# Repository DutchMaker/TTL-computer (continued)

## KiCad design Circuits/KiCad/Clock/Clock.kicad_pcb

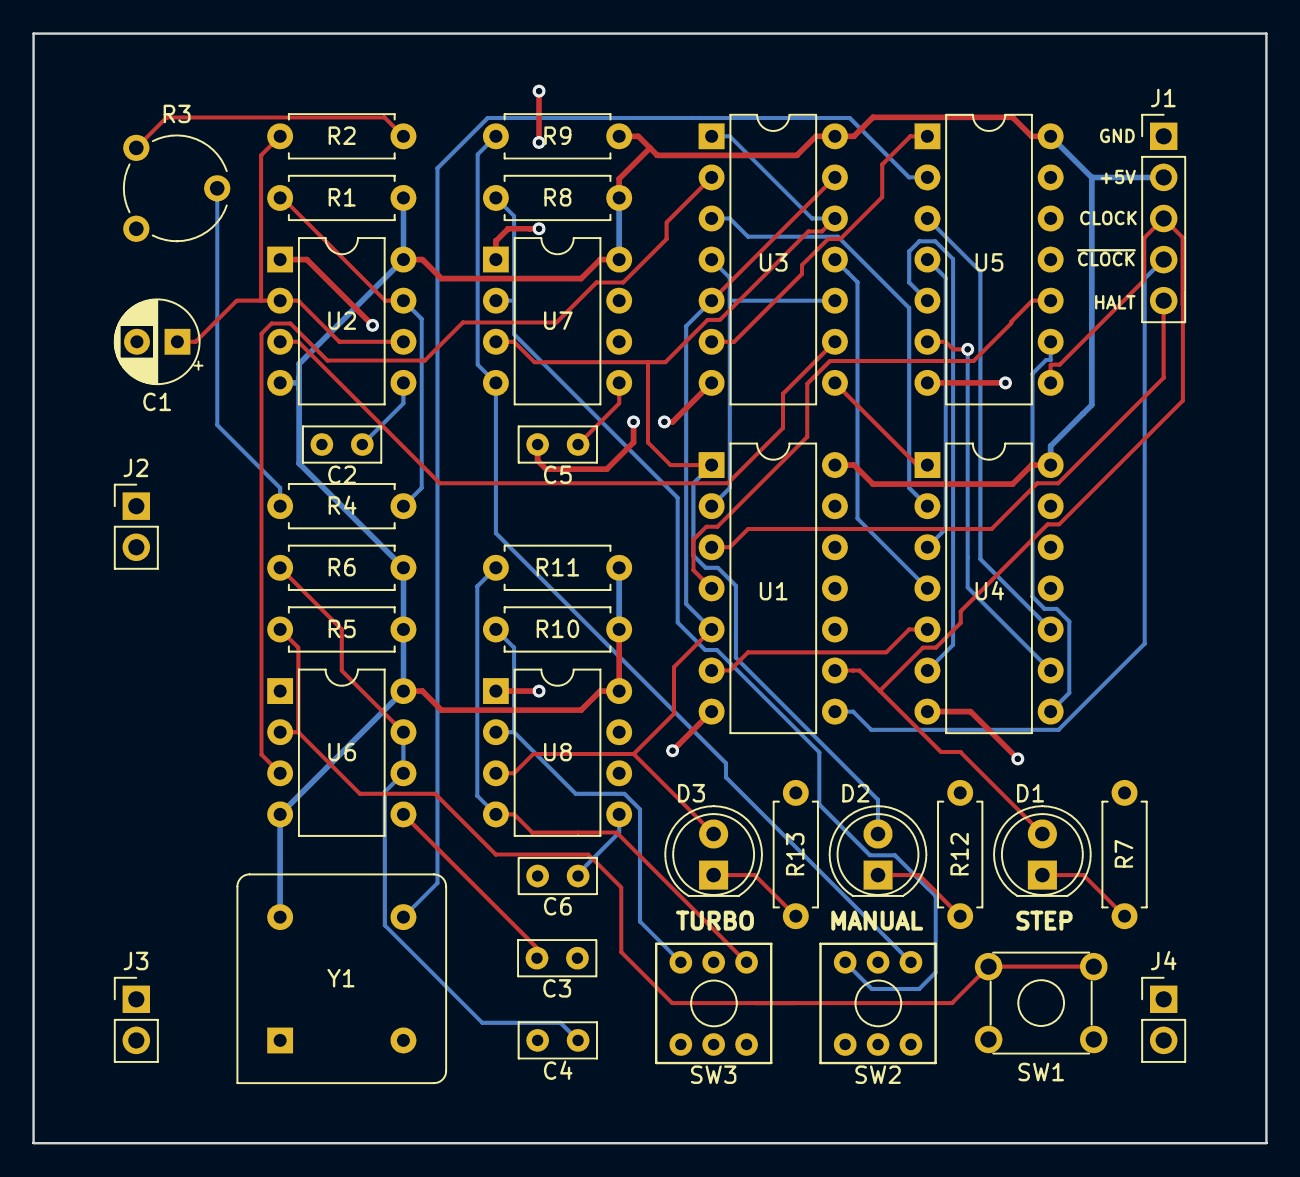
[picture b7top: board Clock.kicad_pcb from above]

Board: 2 copper layers, 76.2 x 68.6 mm, 38 parts (0 on the bottom side), 39 nets.

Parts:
C1: 1uF; CP_Radial_D5.0mm_P2.50mm
C2, C3, C5, C6: 10nF; C_Rect_L4.6mm_W2.0mm_P2.50mm_MKS02_FKP02
C4: 100nF; C_Rect_L4.6mm_W2.0mm_P2.50mm_MKS02_FKP02
D1, D2, D3: LED; LED_D5.0mm
J1: Conn_01x05_Male; PinHeader_1x05_P2.54mm_Vertical
J2, J3, J4: Conn_01x02_Male; PinHeader_1x02_P2.54mm_Vertical
R1, R4, R5, R8, R9, R10, R11: 1K; R_Axial_DIN0207_L6.3mm_D2.5mm_P7.62mm_Horizontal
R2: 47K; R_Axial_DIN0207_L6.3mm_D2.5mm_P7.62mm_Horizontal
R3: 1M; Potentiometer_Piher_PT-6-V_Vertical
R6: 1M; R_Axial_DIN0207_L6.3mm_D2.5mm_P7.62mm_Horizontal
R7, R12, R13: 330; R_Axial_DIN0207_L6.3mm_D2.5mm_P7.62mm_Horizontal
SW1: SW_Push; SW_6mm_Tact
SW2, SW3: SW_Push_SPDT; Switch
U1: 74x04; DIP-14_W7.62mm
U2, U6, U7, U8: 555; DIP-8_W7.62mm
U3, U5: 74x08; DIP-14_W7.62mm
U4: 74x32; DIP-14_W7.62mm
Y1: 1 MHz; Oscillator_DIP-8_v2

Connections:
+5V: J1.2, R1.2, R5.2, R6.1, R8.2, R9.2, R10.2, R11.2, U1.14, U2.4, U2.8, U3.14, U4.14, U5.14, U6.4, U6.8, U7.8, U8.8, Y1.1
CLK_HLT: J1.5, U1.3
CLK_MAN: U3.2, U6.3
CLK_MAN_EN: D2.2, U1.1, U3.1, U3.12, U7.3
CLK_TURBO: U5.2, Y1.3
CLK_TURBO_EN: D3.2, U1.5, U3.5, U3.13, U8.3
CLK_VAR: U2.3, U3.9
CLOCK: D1.2, J1.3, U1.9, U5.8
GND: C1.2, C2.2, C3.2, C4.2, C5.2, C6.2, J1.1, R7.2, R12.2, R13.2, SW1.1, SW2.2, SW3.2, U1.7, U2.1, U3.7, U4.7, U5.7, U6.1, U7.1, U7.6, U8.1, U8.6, Y1.2
unnamed: C1.1, R2.1, U2.2, U2.6
unnamed: C2.1, U2.5
unnamed: C3.1, U6.5
unnamed: C4.1, R6.2, U6.6, U6.7
unnamed: C5.1, U7.5
unnamed: C6.1, U8.5
unnamed: D1.1, R7.1
unnamed: D2.1, R12.1
unnamed: D3.1, R13.1
unnamed: R1.1, R4.1, U2.7
unnamed: R2.2, R3.3
unnamed: R3.2, R4.2
unnamed: R5.1, SW1.2, U6.2
unnamed: R8.1, SW2.1, U7.2
unnamed: R9.1, SW2.3, U7.4
unnamed: R10.1, SW3.1, U8.2
unnamed: R11.1, SW3.3, U8.4
unnamed: U1.2, U3.4, U3.10
unnamed: U1.4, U5.10
unnamed: U1.6, U4.5
unnamed: U3.3, U4.2
unnamed: U3.6, U5.1
unnamed: U3.8, U4.1
unnamed: U3.11, U4.4
unnamed: U4.3, U5.4
unnamed: U4.6, U5.5
unnamed: U4.8, U5.9
unnamed: U4.9, U5.6
unnamed: U4.10, U5.3
~CLOCK: J1.4, U1.8

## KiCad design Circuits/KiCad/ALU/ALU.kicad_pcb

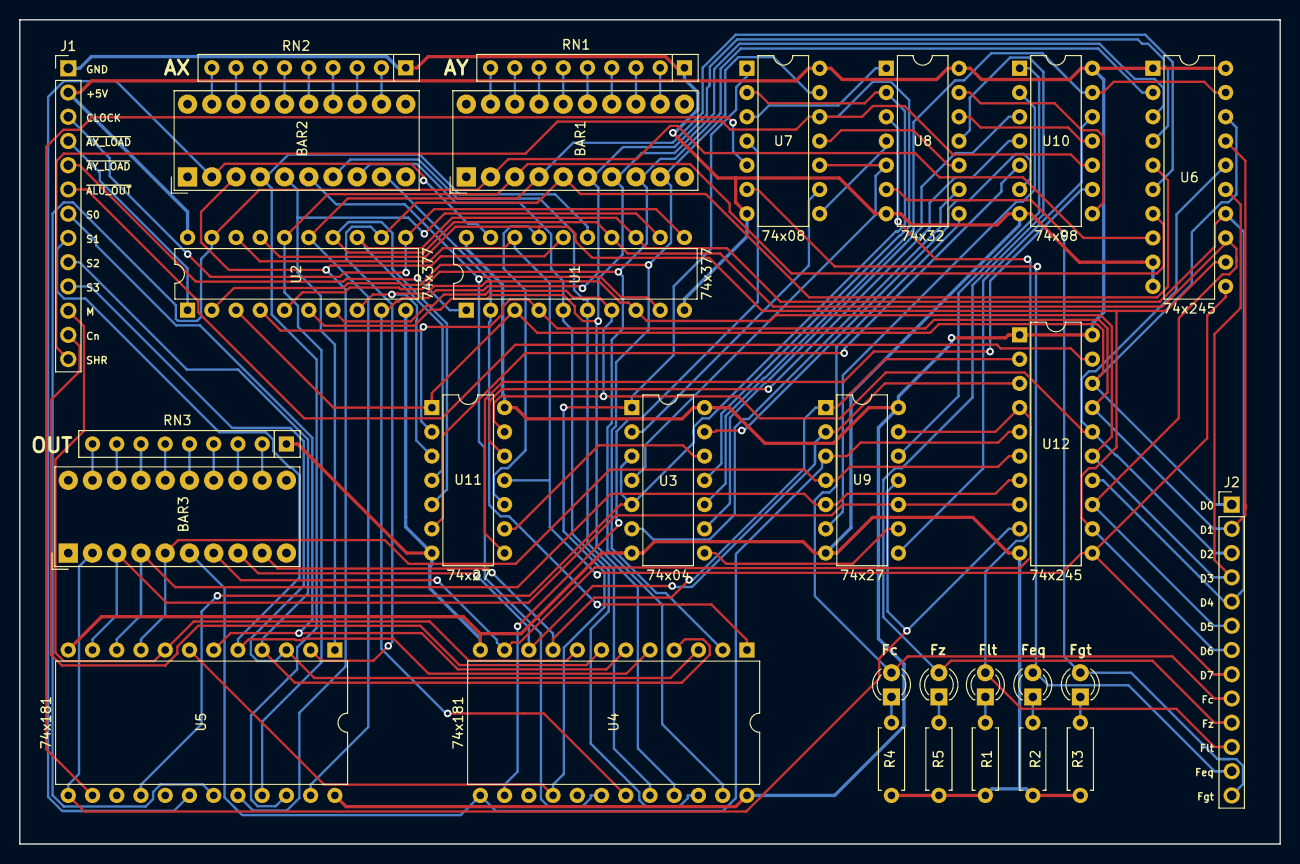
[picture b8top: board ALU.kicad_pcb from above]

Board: 2 copper layers, 132.1 x 86.4 mm, 30 parts (0 on the bottom side), 102 nets.

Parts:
BAR1, BAR2, BAR3: HDSP-4830_2; HDSP-4830
D1: Flt; LED_D3.0mm
D2: Feq; LED_D3.0mm
D3: Fgt; LED_D3.0mm
D4: Fc; LED_D3.0mm
D5: Fz; LED_D3.0mm
J1, J2: Conn_01x13_Male; PinHeader_1x13_P2.54mm_Vertical
R1, R2, R3, R4, R5: 470; R_Axial_DIN0207_L6.3mm_D2.5mm_P7.62mm_Horizontal
RN1, RN2, RN3: 470; R_Array_SIP9
U1, U2: 74x377; DIP-20_W7.62mm
U3: 74x04; DIP-14_W7.62mm
U4, U5: 74x181; DIP-24_W15.24mm
U6, U12: 74x245; DIP-20_W7.62mm
U7, U10: 74x08; DIP-14_W7.62mm
U8: 74x32; DIP-14_W7.62mm
U9, U11: 74x27; DIP-14_W7.62mm

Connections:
+5V: J1.2, U1.20, U2.20, U3.14, U4.24, U5.24, U6.1, U6.20, U7.14, U8.14, U9.14, U10.14, U11.14, U12.1, U12.20
/A=B_A: U4.14, U7.4
/A=B_B: U5.14, U7.5
/Cn4_A: U3.1, U4.16, U5.7, U7.1
/Cn4_B: U3.3, U3.5, U5.16, U7.2, U8.2
CLOCK: J1.3, U1.11, U2.11
Cn: J1.12, U4.7
DATA_BUS0: J2.1, U1.3, U2.3, U6.18, U11.1, U12.18
DATA_BUS1: J2.2, U1.4, U2.4, U6.17, U11.2, U12.17
DATA_BUS2: J2.3, U1.7, U2.7, U6.16, U11.13, U12.16
DATA_BUS3: J2.4, U1.8, U2.8, U6.15, U11.3, U12.15
DATA_BUS4: J2.5, U1.13, U2.13, U6.14, U11.4, U12.14
DATA_BUS5: J2.6, U1.14, U2.14, U6.13, U11.5, U12.13
DATA_BUS6: J2.7, U1.17, U2.17, U6.12, U11.10, U12.12
DATA_BUS7: J2.8, U1.18, U2.18, U6.11, U11.11, U12.11
Fc: D4.2, J2.9, U8.8
Feq: D2.2, J2.12, U7.6
Fgt: D3.2, J2.13, U8.6
Flt: D1.2, J2.11, U8.3
Fz: D5.2, J2.10, U8.11
GND: J1.1, R1.1, R2.1, R3.1, R4.1, R5.1, RN1.1, RN2.1, RN3.1, U1.10, U2.10, U3.7, U4.12, U5.12, U6.9, U6.10, U7.7, U8.7, U9.7, U10.7, U11.7, U12.10
M: J1.11, U4.8, U5.8
unnamed: BAR1.2, U2.19, U5.19, U6.8
unnamed: BAR1.3, U2.16, U5.21, U6.7
unnamed: BAR1.4, U2.15, U5.23, U6.6
unnamed: BAR1.5, U2.12, U5.2, U6.5
unnamed: BAR1.6, U2.9, U4.19, U6.4
unnamed: BAR1.7, U2.6, U4.21, U6.3
unnamed: BAR1.8, U2.5, U4.23, U6.2
unnamed: BAR1.12, RN1.2
unnamed: BAR1.13, RN1.3
unnamed: BAR1.14, RN1.4
unnamed: BAR1.15, RN1.5
unnamed: BAR1.16, RN1.6
unnamed: BAR1.17, RN1.7
unnamed: BAR1.18, RN1.8
unnamed: BAR1.19, RN1.9
unnamed: BAR2.2, U1.19, U5.18
unnamed: BAR2.3, U1.16, U5.20
unnamed: BAR2.4, U1.15, U5.22
unnamed: BAR2.5, U1.12, U5.1
unnamed: BAR2.6, U1.9, U4.18
unnamed: BAR2.7, U1.6, U4.20
unnamed: BAR2.8, U1.5, U4.22
unnamed: BAR2.9, U1.2, U4.1
unnamed: BAR2.12, RN2.2
unnamed: BAR2.13, RN2.3
unnamed: BAR2.14, RN2.4
unnamed: BAR2.15, RN2.5
unnamed: BAR2.16, RN2.6
unnamed: BAR2.17, RN2.7
unnamed: BAR2.18, RN2.8
unnamed: BAR2.19, RN2.9
unnamed: BAR3.2, U5.13, U9.11, U12.9
unnamed: BAR3.3, U5.11, U9.10, U12.8
unnamed: BAR3.4, U5.10, U9.5, U12.7
unnamed: BAR3.5, U5.9, U9.4, U12.6
unnamed: BAR3.6, U4.13, U9.3, U12.5
unnamed: BAR3.7, U4.11, U9.13, U12.4
unnamed: BAR3.8, U4.10, U9.2, U12.3
unnamed: BAR3.9, U4.9, U9.1, U12.2
unnamed: BAR3.12, RN3.2
unnamed: BAR3.13, RN3.3
unnamed: BAR3.14, RN3.4
unnamed: BAR3.15, RN3.5
unnamed: BAR3.16, RN3.6
unnamed: BAR3.17, RN3.7
unnamed: BAR3.18, RN3.8
unnamed: BAR3.19, RN3.9
unnamed: D1.1, R1.2
unnamed: D2.1, R2.2
unnamed: D3.1, R3.2
unnamed: D4.1, R4.2
unnamed: D5.1, R5.2
unnamed: U3.2, U7.9
unnamed: U3.4, U7.10, U8.5
unnamed: U3.6, U8.9
unnamed: U3.8, U9.9
unnamed: U7.3, U8.1
unnamed: U7.8, U8.4
unnamed: U7.11, U8.10
unnamed: U9.12, U10.1
unnamed: U9.6, U10.2
unnamed: U3.9, U10.3
unnamed: U10.4, U11.12
unnamed: U10.5, U11.6
unnamed: U3.13, U10.6
unnamed: U10.9, U11.8
unnamed: U8.12, U10.11
unnamed: U9.8, U10.12
unnamed: U3.12, U11.9
S0: J1.7, U4.6, U5.6
S1: J1.8, U4.5, U5.5
S2: J1.9, U4.4, U5.4
S3: J1.10, U4.3, U5.3
SHR: J1.13, U3.11, U7.12, U10.10
SHRc: BAR1.9, U2.2, U4.2, U7.13
SHRz: U8.13, U10.8
~ALU_OUT: J1.6, U12.19
~AX_LOAD: J1.4, U2.1
~AY_LOAD: J1.5, U1.1
~SHR: U3.10, U6.19, U10.13

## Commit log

2018-04-11 Added clock mode toggle logic
2018-04-11 Added readme
2018-04-12 First revision of Clock module circuit (untested at this point)
2018-04-12 Creating hierarchical schematic
2018-04-12 Built and tested Clock module
2018-04-12 Added PDF print of Visio file
2018-04-13 Started work on Program Counter
2018-04-14 Just more work in progress...
2018-04-15 Removed ROM loader idea from architecture
2018-04-20 Added datasheets
2018-04-29 Copied X register to Y register
2018-04-29 Bit of thinking on the instruction set
2018-04-30 Started using Logisim. Testing ALU stuff
2018-05-01 Did some work on ALU
2018-05-02 Figured out the truth table for my ALU
2018-05-03 Added A and B register schematic
2018-05-04 Added some schematics
2018-05-05 Improved ALU and instructions (ALU now takes data from all registers)
2018-05-05 Renamed registers X and Y to C and D.
    ALU now has its own internal accumulator register.
2018-05-11 Updated folder structure and working out the memory module
2018-05-14 Completed memory circuit diagram (untested)
2018-05-14 Added Stack Pointer schematic (untested)
2018-05-15 Added empty MAR module schematic
2018-05-25 Finished MAR
2019-03-12 temp
2019-03-12 Updated component reference
2019-03-13 Fixed 74ls377 symbol
2019-03-13 Added 29C040 ROM component for controller-sequencer module
2019-03-13 Work in progress on controller/sequencer
2019-03-15 Documenting Controller-Sequencer
2019-03-18 Working out logic for controller/sequencer in Logisim
2019-03-19 Working instruction decoder
2019-03-19 Updated architecture overview
2019-03-21 Fixed race condition in instruction decoder
2019-03-21 Extended instruction decoder simulation to load all 48 bits
2019-03-21 Updated a bit of doc
2019-03-22 Added hex display to instruction decoder
2019-03-24 Implemented program counter in Logisim
2019-03-24 Logisim libraries moved
2019-03-25 Added Stack Pointer to Logisim
2019-03-25 Created ALU in Logisim
2019-03-25 Some renaming and cleaning in Logisim
2019-03-25 Implemented memory access register in Logisim
2019-03-25 Added memory circuit in Logisim
2019-03-26 Manual control line input is all high-enabled now
2019-03-26 Fixed load error in Logisim project
2019-03-26 Added instruction decoder to main circuit in Logisim (not functioning atm)
2019-03-27 First instruction (NOP) is being executed in Logisim
2019-03-28 Defined a simple microcode programming language
2019-03-28 Started work on a compile for the microcode (.NET Core console app)
2019-03-30 Microcode compilation working (untested)
2019-03-31 Fixed bug in microcode compiler addressing
2019-03-31 Fixed incorrect tstate translation in compiler
2019-03-31 Moved TSTATE_reset to separate tstate. Going to add registers to decoder, see if tstate_reset can be moved back after that
2019-03-31 MVI A instruction working in Logisim.
    Controller needs redesigning!
2019-04-01 Running a program of 5 instructions in Logisim. TSTATE_reset must be in separate tstate atm.
2019-04-01 Rebuilding the controller
2019-04-01 Previously tested instructions work with new Controller design
2019-04-02 Updated some documentation
2019-04-03 Implemented more instructions
2019-04-03 Started work on the Assembler
2019-04-03 Working on assembler
2019-04-06 First version of Assembler is done
2019-04-06 Fixed assembler bug. Flipped ROM_BOOT flag to active low for easier reset.
2019-04-06 README update
2019-04-06 Implemented CMP instruction
2019-04-06 Implemented additional instructions to load data into ALU registers
2019-04-07 Renamed ALU registers and added them to MOV and MVI. Removed MVA instruction.
2019-04-07 Small improvement in mcc
2019-04-07 Implemented AND, OR, XOR, INC, DEC
2019-04-07 Carry can be set and cleared now. Trying to figure out SBC and SHR
2019-04-08 Right shift implemented
2019-04-08 Added support for address variables. LD now supports AX&AY
2019-04-08 Testing conditional jumps
2019-04-08 Implemented and tested all jump instructions
2019-04-08 Hello World working
2019-04-09 Moved Logisim project. Started work on Assembly language reference
2019-04-10 Assembly Language Reference done
2019-04-10 Markdown layout fixes
2019-04-10 Implement indirect load/store instructions in assembler
2019-04-10 Added support for string data in assembly. Fixed assembler bugs. Added example Hello World program.
2019-04-11 Renamed microcode instructions LDX/STX to LDR/STR to differentiate them from LDX/STX that is implemented by the assembler.
2019-04-11 Implemented zero page memory
2019-04-11 Added zero page addressing support for LDX and STX
2019-04-11 Reference layout fix
2019-04-12 Changed "MOV source target" to be "MOV target source" so it's more in line with the other instructions (and other assembly languages for that matter)
2019-04-16 Added LCD display
2019-04-17 Playing around with loading a bitmap (slowwwwwly)
2019-04-24 Switched to Linux, so line endings....
2019-04-25 Double the t-states and double the instructions (work in progress...)
2019-04-26 Condition return instructions. Updated docs
2019-04-27 Added CALLC instructions
2019-04-27 Added PUSH/POP instructions
2019-04-29 Working on module that outputs VRAM to LCD while program is running
2019-07-24 Revising all KiCad circuits and routing PCB's. Starting with the Clock module.
2019-07-26 Work in progress on schematics and PCBs
2019-07-26 Finished Program Counter schematic & PCB
2019-07-26 Added Stack Pointer schematics & PCB. Rerouted Clock based autorouter output
2019-07-27 Created Flags Register schematic and PCB
2019-07-27 Removed unused files
2019-07-27 Updated a few Clock component footprints according to actual measurements
2019-07-27 Finished Flag Register schematic & PCB
2019-07-29 Made sure spacing between headers is always 2.54mm pitch
2019-08-01 Created ALU schematic and PCB
2019-08-02 Moved stack address output control to stack circuit in Logisim
2019-08-02 Updated Stack Pointer schematic and PCB
2019-08-02 Moved Program Counter output control to Program Counter circuit in Logisim
2019-08-03 Updated Program Counter schematic and PCB
2019-08-03 Updated pin header row pitch
2019-08-03 Schematic for Memory Access Register
2019-08-04 First draft of schematic for Memory Access Register
2019-08-05 Memory schematic in progress
2019-08-08 Removed absolute library paths (see readme)
2019-08-08 Built Clock circuit on PCB and updated design accordingly. Added footprint for a few exotic components
2019-08-09 Built Stack Pointer and Program Counter on PCB
2019-08-09 Updated order of control lines and added printable guide to put on top of bar graph on PCB later on
2019-08-10 Work in progress on MAR pcb layout
2019-08-10 Routed MAR PCB
2019-08-11 Finished Memory & Memory Access Register PCB
2019-08-11 Rerouted Register PCB and fixed pin header pitch
2019-08-11 Added Instruction Register circuit and PCB
2019-08-12 Created Controller schematic
2019-08-14 Layed out Controller PCB. Started work on Main Board circuit that will connect all modules
2019-08-15 Autorouted Controller
2019-08-15 Main board PCB layed out
2019-08-15 Removed old (obsolete) circuit schematics
2019-08-16 Rerouted Controller and Main board (needs work)
2019-08-16 Finished Main Board PCB
2019-08-16 Finished Controller PCB
2019-08-16 Last PCB's put into production
2019-08-16 Fixed bug in microcode. Writing a test program that runs tests for all instructions.
2019-08-16 Added counter program in test
2019-08-18 Finished test program
2019-08-18 Fixed issue with CALL in microcode
2019-08-18 Updated status in README
2019-08-26 Removed inverter from clock line on RAM (in Logisim only)
2019-08-27 Some documentation
2019-08-27 Added picture of completed Memory PCB
2019-08-28 Added board error to doc
2019-08-29 Updated issues
2019-08-29 Added pictures of completed PCBs
2019-09-04 Bit more ideas for next version
2019-09-04 Bit of doc on controller change
2019-09-04 Revised controller - notes following
2019-09-04 Controller PCB rev2
2019-09-09 Added schematics as PDF
2019-09-10 Added picture
